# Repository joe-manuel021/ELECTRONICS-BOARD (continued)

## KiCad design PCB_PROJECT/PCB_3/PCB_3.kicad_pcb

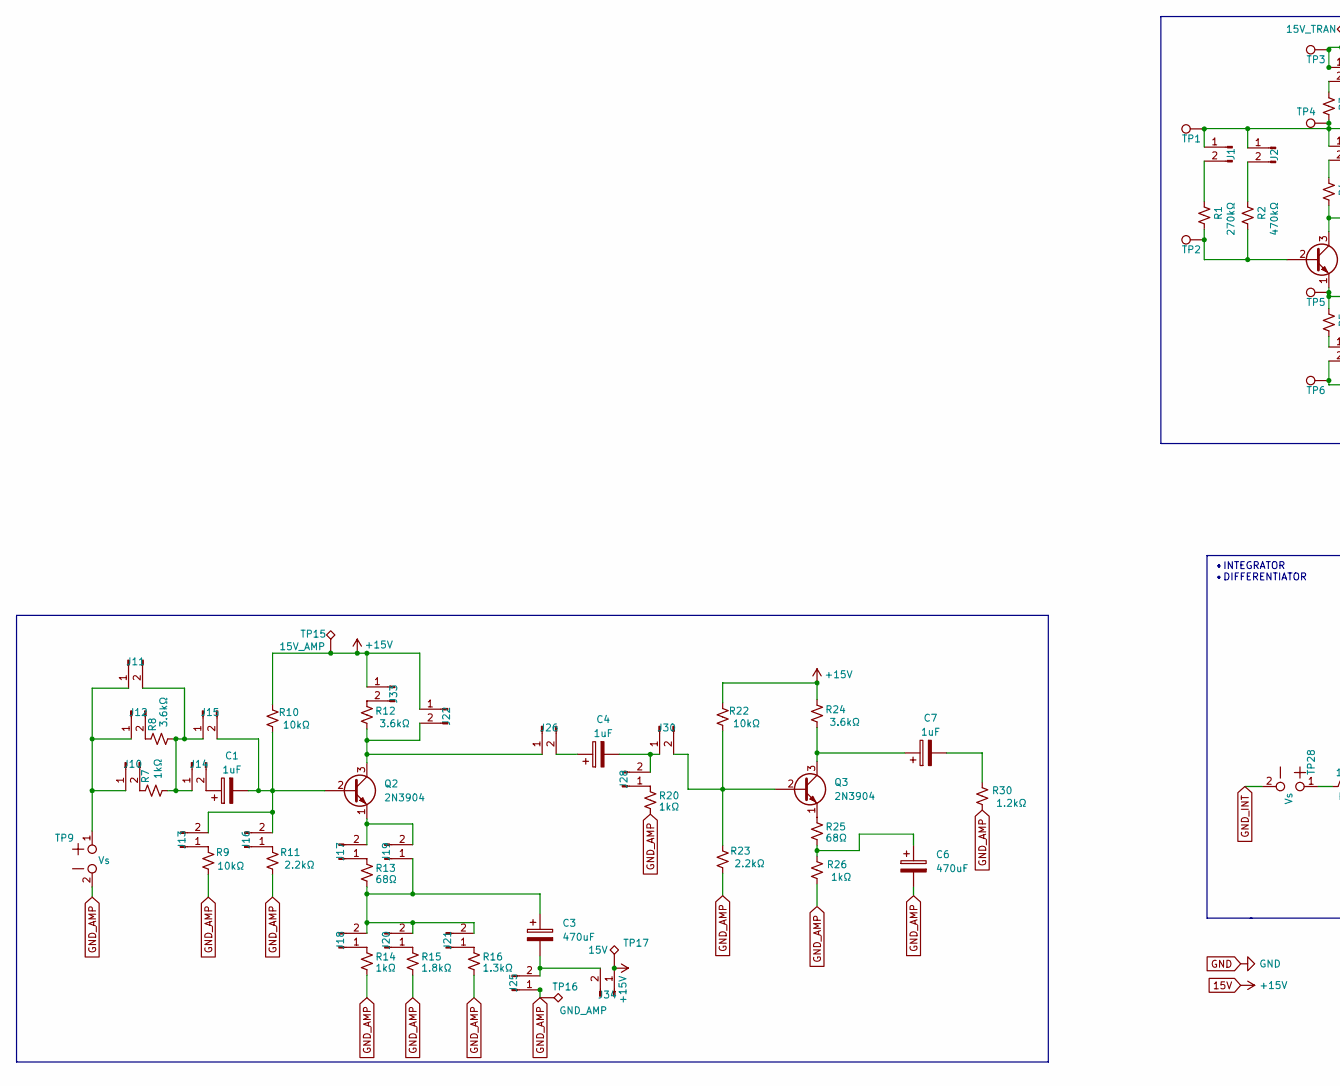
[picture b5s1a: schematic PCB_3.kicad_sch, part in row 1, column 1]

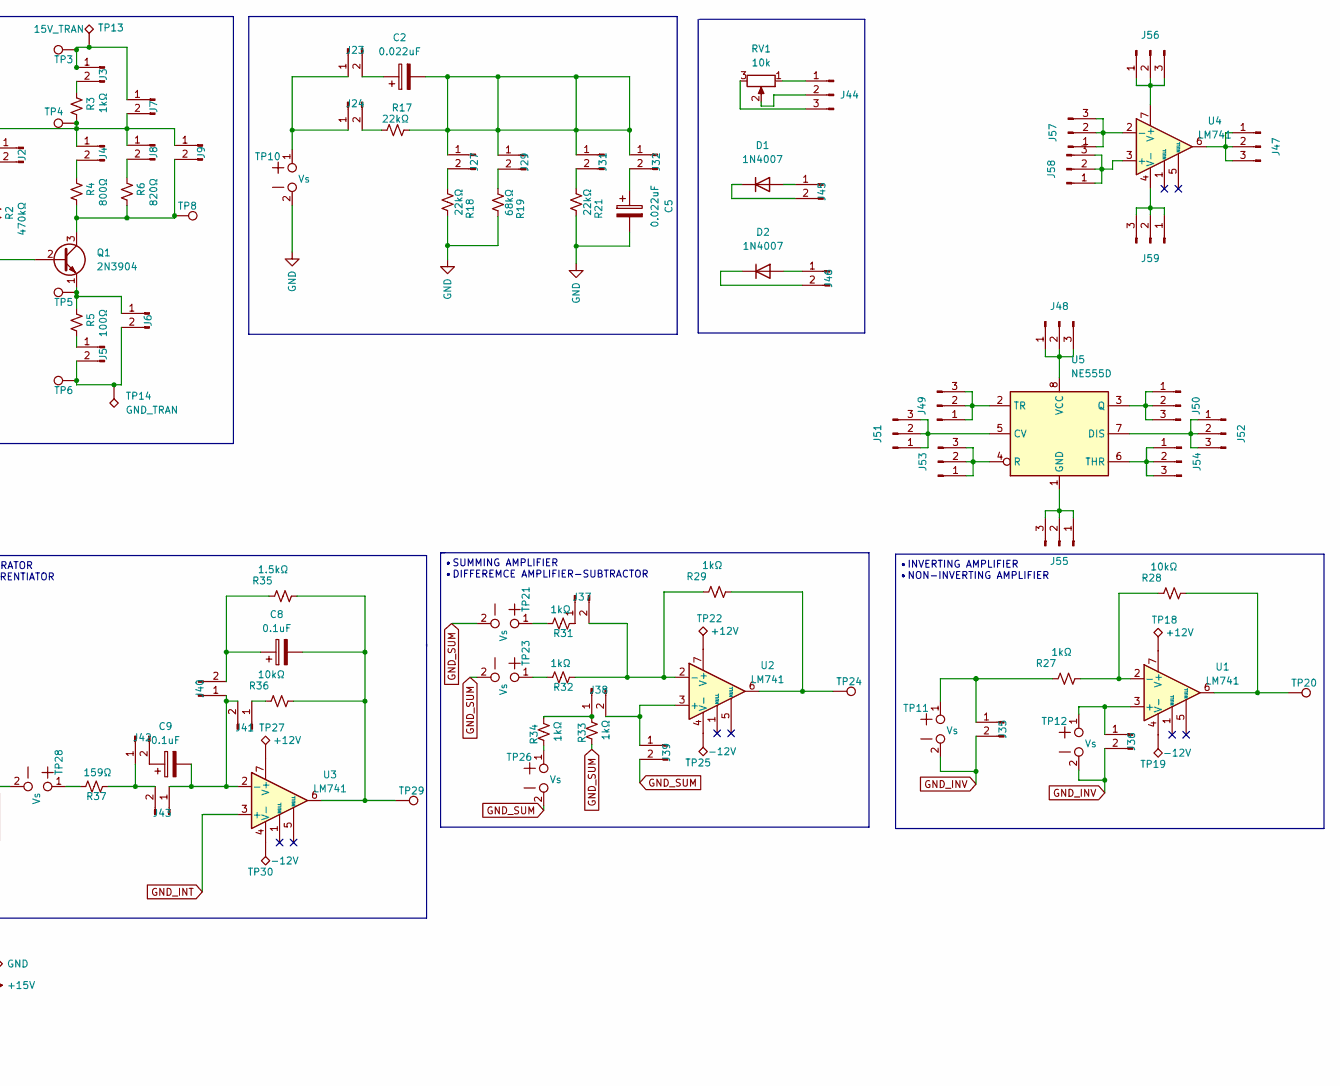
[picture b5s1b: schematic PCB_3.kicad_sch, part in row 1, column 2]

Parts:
C1, C4, C7: 1uF; CP_Radial_D5.0mm_P2.50mm
C2, C5: 0.022uF; 0.022uF_Capacitor
C3, C6: 470uF; CP_Radial_D10.0mm_P5.00mm
C8, C9: 0.1uF; 0.022uF_Capacitor
D1, D2: 1N4007; D_DO-41_SOD81_P10.16mm_Horizontal
J1, J2, J3, J4, J5, J6, J7, J8, J9, J10, J11, J12, J13, J14, J15, J16, J17, J18, J19, J20, J21, J22, J23, J24, J25, J26, J27, J28, J29, J30, J31, J32, J33, J34, J35, J36, J37, J38, J39, J40, J41, J42, J43, J45, J46: PinHeader_1x02_P2.54mm_Vertical_Blue
J44: W; PinHeader_1x03_P2.54mm_Vertical
J47, J48, J49, J50, J51, J52, J53, J54, J55, J56, J57, J58, J59: Conn_01x03_Male; PinHeader_1x03_P2.54mm_Vertical
Q1, Q2, Q3: 2N3904; TO-92_Inline
R1: 270kΩ; R_Axial_DIN0207_L6.3mm_D2.5mm_P10.16mm_Horizontal
R2: 470kΩ; R_Axial_DIN0207_L6.3mm_D2.5mm_P10.16mm_Horizontal
R3, R7, R14, R20, R26, R27, R29, R31, R32, R33, R34: 1kΩ; R_Axial_DIN0207_L6.3mm_D2.5mm_P10.16mm_Horizontal
R4: 800Ω; R_Axial_DIN0207_L6.3mm_D2.5mm_P10.16mm_Horizontal
R5: 100Ω; R_Axial_DIN0207_L6.3mm_D2.5mm_P10.16mm_Horizontal
R6: 820Ω; R_Axial_DIN0207_L6.3mm_D2.5mm_P10.16mm_Horizontal
R8, R12, R24: 3.6kΩ; R_Axial_DIN0207_L6.3mm_D2.5mm_P10.16mm_Horizontal
R9, R10, R22, R28, R36: 10kΩ; R_Axial_DIN0207_L6.3mm_D2.5mm_P10.16mm_Horizontal
R11, R23: 2.2kΩ; R_Axial_DIN0207_L6.3mm_D2.5mm_P10.16mm_Horizontal
R13, R25: 68Ω; R_Axial_DIN0207_L6.3mm_D2.5mm_P10.16mm_Horizontal
R15: 1.8kΩ; R_Axial_DIN0207_L6.3mm_D2.5mm_P10.16mm_Horizontal
R16: 1.3kΩ; R_Axial_DIN0207_L6.3mm_D2.5mm_P10.16mm_Horizontal
R17, R18, R21: 22kΩ; R_Axial_DIN0207_L6.3mm_D2.5mm_P10.16mm_Horizontal
R19: 68kΩ; R_Axial_DIN0207_L6.3mm_D2.5mm_P10.16mm_Horizontal
R30: 1.2kΩ; R_Axial_DIN0207_L6.3mm_D2.5mm_P10.16mm_Horizontal
R35: 1.5kΩ; R_Axial_DIN0207_L6.3mm_D2.5mm_P10.16mm_Horizontal
R37: 159Ω; R_Axial_DIN0207_L6.3mm_D2.5mm_P10.16mm_Horizontal
RV1: 10k; Potentiometer_Alps_RK09Y11_Single_Horizontal
TP1, TP2, TP3, TP4, TP5, TP6, TP8: 2.5_TP_1.5
TP9, TP10, TP11, TP12, TP21, TP23, TP26, TP28: Vs; TestPoint_Pith10mm_Drill4mm
TP13: 15V_TRAN; POWER_4MM
TP14: GND_TRAN; GND_4MM
TP15: 15V_AMP; POWER_4MM
TP16: GND_AMP; GND_4MM
TP17: 15V; POWER_4MM
TP18, TP22, TP27: +12V; GND_4MM
TP19, TP25, TP30: -12V; POWER_4MM
TP20, TP24, TP29: GND_4MM
U1, U2, U3, U4: LM741; DIP-8_W10.16mm_LongPads
U5: NE555D; DIP-8_W7.62mm_LongPads

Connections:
15V: J22.1, J33.1, J34.1, R10.2, R22.2, R24.2, TP15.1, TP17.1
GND: C5.2, R18.2, R19.2, R21.2, TP10.2
GND_AMP: C6.2, J25.1, R9.1, R11.1, R14.1, R15.1, R16.1, R20.1, R23.1, R26.1, R30.1, TP9.2, TP16.1
GND_INT: TP28.2, U3.3 (+)
GND_INV: J35.2, J36.2, TP11.2, TP12.2
GND_SUM: J39.2, R33.2, TP21.2, TP23.2, TP26.2
unnamed: C1.1, J14.2
unnamed: C1.2, J13.2, J15.2, J16.2, Q2.2 (B), R10.1
unnamed: C2.1, J23.2
unnamed: C2.2, J27.1, J29.1, J31.1, J32.1, R17.2
unnamed: C3.1, J18.2, J19.1, J20.2, J21.2, R13.1
unnamed: C3.2, J25.2, J34.2
unnamed: C4.1, J26.2
unnamed: C4.2, J28.2, J30.1
unnamed: C5.1, J32.2
unnamed: C6.1, R25.1, R26.2
unnamed: C7.1, Q3.3 (C), R24.1
unnamed: C7.2, R30.2
unnamed: C8.1, J40.2, R35.2
unnamed: C8.2, R35.1, R36.1, TP29.1, U3.6
unnamed: C9.1, J42.2
unnamed: C9.2, J40.1, J41.2, J43.1, U3.2 (-)
unnamed: D1.1 (K), J45.2
unnamed: D1.2 (A), J45.1
unnamed: D2.1 (K), J46.2
unnamed: D2.2 (A), J46.1
unnamed: J1.1, J2.1, J4.1, J7.2, J8.1, J9.1, R3.2, TP1.1, TP4.1
unnamed: J1.2, R1.1
unnamed: J2.2, R2.1
unnamed: J3.1, J7.1, TP3.1, TP13.1
unnamed: J3.2, R3.1
unnamed: J4.2, R4.1
unnamed: J5.1, R5.2
unnamed: J5.2, J6.2, TP6.1, TP14.1
unnamed: J6.1, Q1.1 (E), R5.1, TP5.1
unnamed: J8.2, R6.1
unnamed: J9.2, Q1.3 (C), R4.2, R6.2, TP8.1
unnamed: J10.1, J11.1, J12.1, TP9.1
unnamed: J10.2, R7.2
unnamed: J11.2, J14.1, J15.1, R7.1, R8.1
unnamed: J12.2, R8.2
unnamed: J13.1, R9.2
unnamed: J16.1, R11.2
unnamed: J17.1, R13.2
unnamed: J17.2, J19.2, Q2.1 (E)
unnamed: J18.1, R14.2
unnamed: J20.1, R15.2
unnamed: J21.1, R16.2
unnamed: J22.2, J26.1, Q2.3 (C), R12.1
unnamed: J23.1, J24.1, TP10.1
unnamed: J24.2, R17.1
unnamed: J27.2, R18.1
unnamed: J28.1, R20.2
unnamed: J29.2, R19.1
unnamed: J30.2, Q3.2 (B), R22.1, R23.2
unnamed: J31.2, R21.1
unnamed: J33.2, R12.2
unnamed: J35.1, R27.2, TP11.1
unnamed: J36.1, TP12.1, U1.3 (+)
unnamed: J37.1, R31.2
unnamed: J37.2, R29.2, R32.2, U2.2 (-)
unnamed: J38.1, R33.1, R34.1
unnamed: J38.2, J39.1, U2.3 (+)
unnamed: J41.1, R36.2
unnamed: J42.1, J43.2, R37.2
unnamed: J44.1, RV1.1
unnamed: J44.2, RV1.2
unnamed: J44.3, RV1.3
unnamed: J47.1, J47.2, J47.3, U4.6
unnamed: J48.1, J48.2, J48.3, U5.8 (VCC)
unnamed: J49.1, J49.2, J49.3, U5.2 (TR)
unnamed: J50.1, J50.2, J50.3, U5.3 (Q)
unnamed: J51.1, J51.2, J51.3, U5.5 (CV)
unnamed: J52.1, J52.2, J52.3, U5.7 (DIS)
unnamed: J53.1, J53.2, J53.3, U5.4 (R)
unnamed: J54.1, J54.2, J54.3, U5.6 (THR)
unnamed: J55.1, J55.2, J55.3, U5.1 (GND)
unnamed: J56.1, J56.2, J56.3, U4.7 (V+)
unnamed: J57.1, J57.2, J57.3, U4.2 (-)
unnamed: J58.1, J58.2, J58.3, U4.3 (+)
unnamed: J59.1, J59.2, J59.3, U4.4 (V-)
unnamed: Q1.2 (B), R1.2, R2.2, TP2.1
unnamed: Q3.1 (E), R25.2
unnamed: R27.1, R28.2, U1.2 (-)
unnamed: R28.1, TP20.1, U1.6
unnamed: R29.1, TP24.1, U2.6
unnamed: R31.1, TP21.1
unnamed: R32.1, TP23.1
unnamed: R34.2, TP26.1
unnamed: R37.1, TP28.1
unnamed: TP18.1, U1.7 (V+)
unnamed: TP19.1, U1.4 (V-)
unnamed: TP22.1, U2.7 (V+)
unnamed: TP25.1, U2.4 (V-)
unnamed: TP27.1, U3.7 (V+)
unnamed: TP30.1, U3.4 (V-)

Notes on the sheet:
•INVERTING AMPLIFIER •NON-INVERTING AMPLIFIER
•SUMMING AMPLIFIER •DIFFEREMCE AMPLIFIER-SUBTRACTOR
•INTEGRATOR •DIFFERENTIATOR

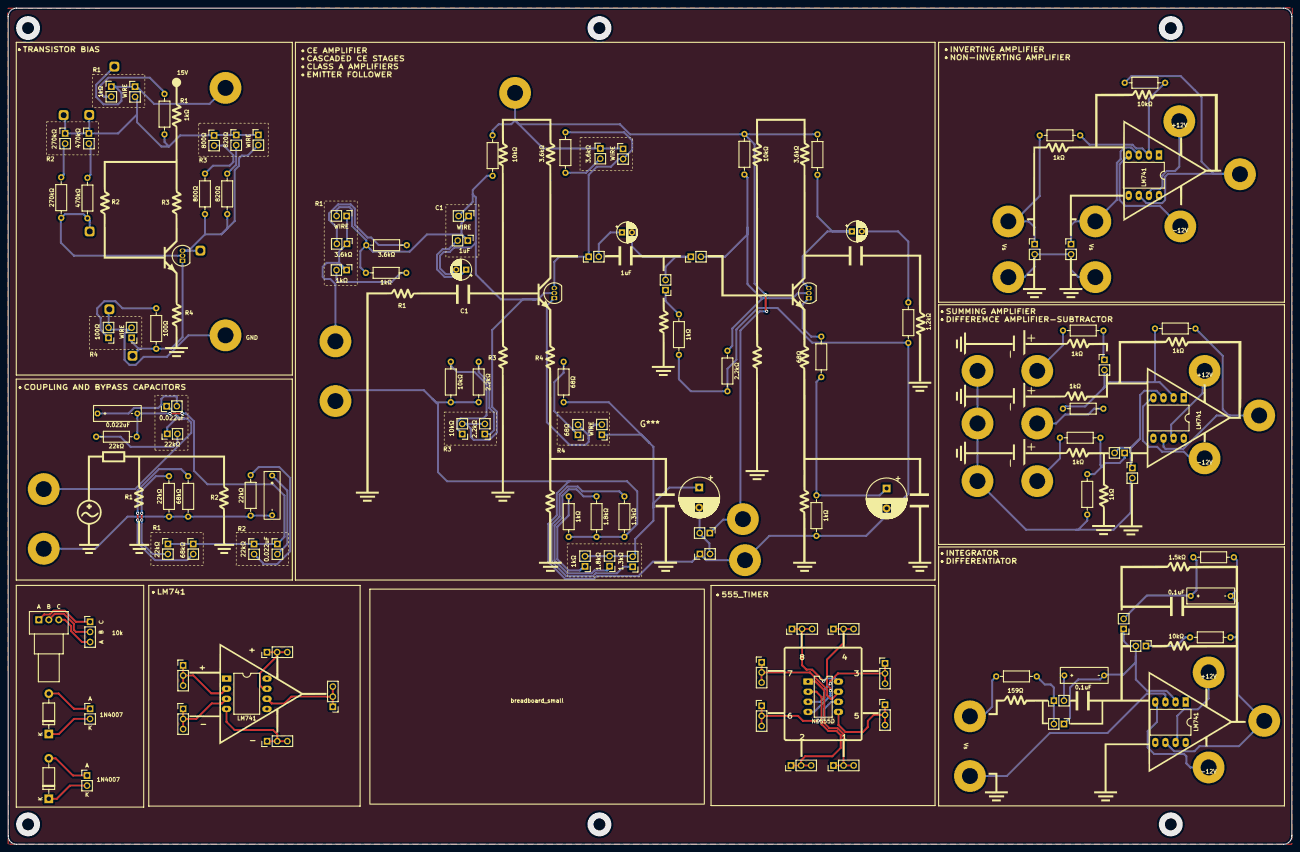
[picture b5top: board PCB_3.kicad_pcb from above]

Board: 2 copper layers, 322.4 x 210.0 mm, 145 parts (0 on the bottom side), 96 nets.

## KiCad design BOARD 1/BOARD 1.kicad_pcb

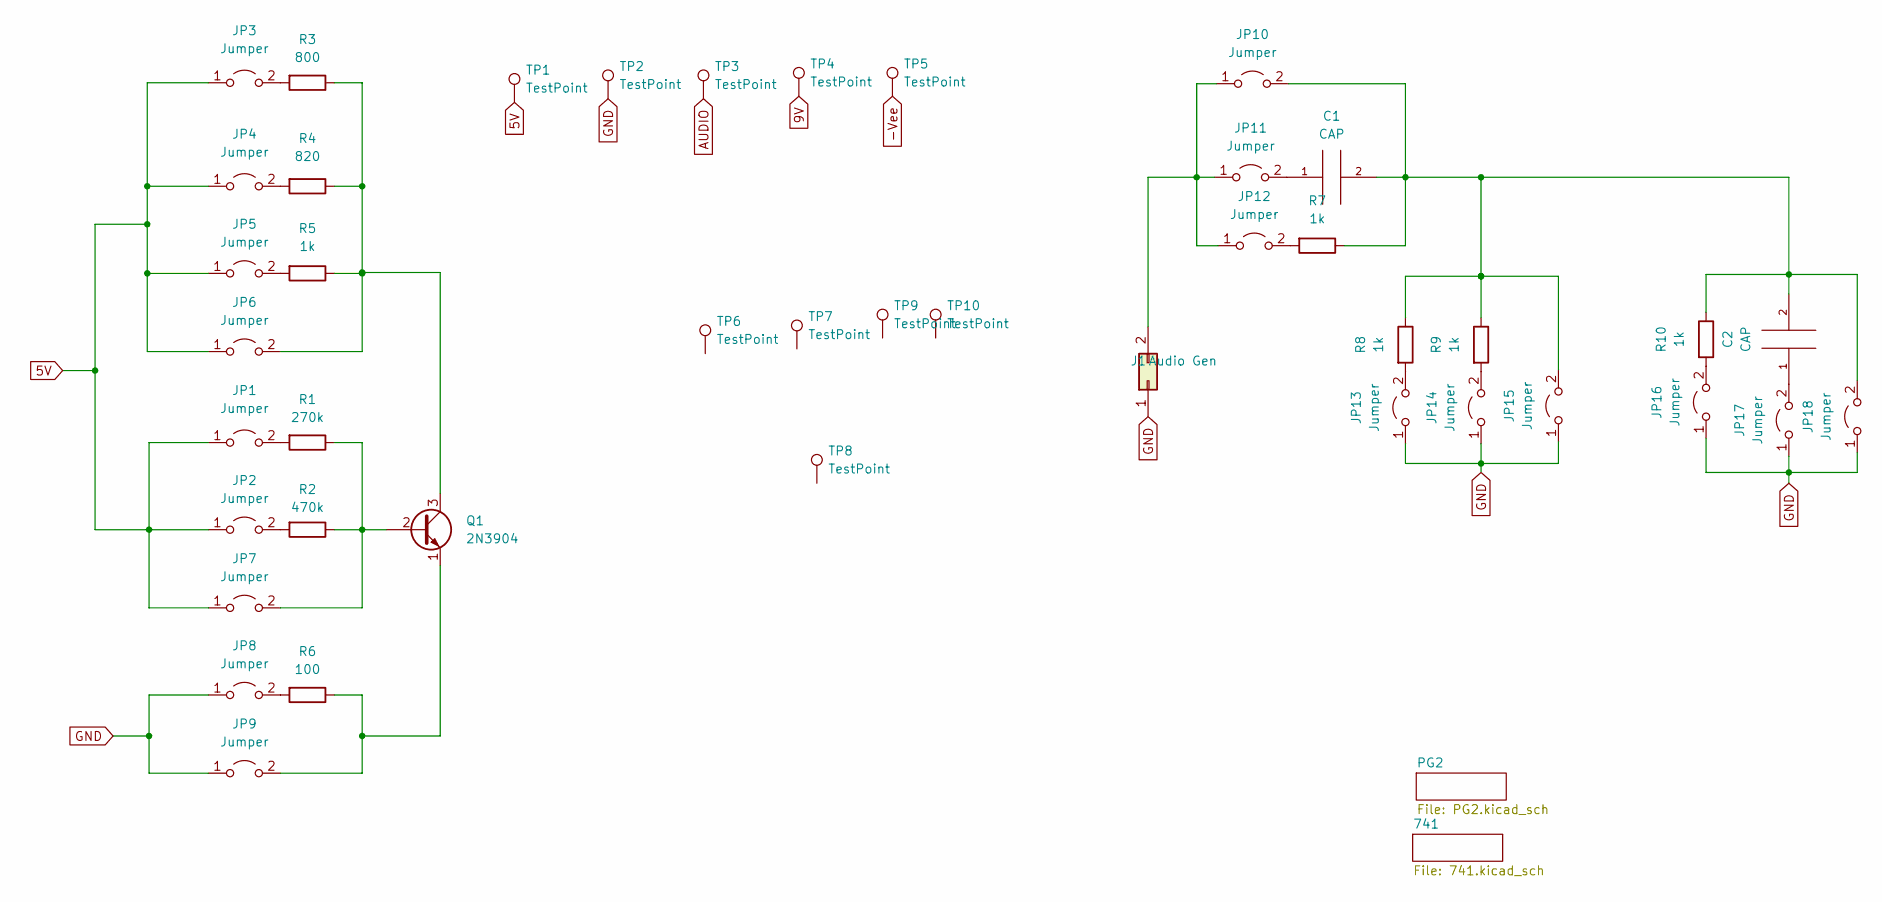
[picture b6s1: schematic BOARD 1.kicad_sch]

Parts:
C1, C2: CAP; CP_Radial_D5.0mm_P2.00mm
J1: Audio Gen; PinHeader_1x02_P2.54mm_Vertical
JP1, JP2, JP3, JP4, JP5, JP6, JP7, JP8, JP9, JP10, JP11, JP12, JP13, JP14, JP15, JP16, JP17, JP18: Jumper; PinHeader_1x02_P2.54mm_Vertical
Q1: 2N3904; TO-92_Inline
R1: 270k; R_Axial_DIN0309_L9.0mm_D3.2mm_P12.70mm_Horizontal
R2: 470k; R_Axial_DIN0309_L9.0mm_D3.2mm_P12.70mm_Horizontal
R3: 800; R_Axial_DIN0309_L9.0mm_D3.2mm_P12.70mm_Horizontal
R4: 820; R_Axial_DIN0309_L9.0mm_D3.2mm_P12.70mm_Horizontal
R5, R7, R8, R9, R10: 1k; R_Axial_DIN0309_L9.0mm_D3.2mm_P12.70mm_Horizontal
R6: 100; R_Axial_DIN0309_L9.0mm_D3.2mm_P12.70mm_Horizontal
TP1, TP2, TP3, TP4, TP5, TP6, TP7, TP8, TP9, TP10: TestPoint; TestPoint_Plated_Hole_D5.0mm

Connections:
5V: JP1.1 (A), JP2.1 (A), JP3.1 (A), JP4.1 (A), JP5.1 (A), JP6.1 (A), JP7.1 (A), TP1.1; also elsewhere on the board
GND: J1.1 (Pin_a1), JP8.1 (A), JP9.1 (A), JP13.1 (A), JP14.1 (A), JP15.1 (A), JP16.1 (A), JP17.1 (A), JP18.1 (A), TP2.1; also elsewhere on the board
unnamed 6: C1.1, JP11.2 (B); also elsewhere on the board
unnamed 7: C1.2, JP10.2 (B), JP15.2 (B), R7.1, R8.1, R9.1; also elsewhere on the board
unnamed: C2.1, JP17.2 (B)
unnamed 9: C2.2, JP18.2 (B), R10.1; also elsewhere on the board
unnamed 20: J1.2 (Pin_b1), JP10.1 (A), JP11.1 (A), JP12.1 (A); also elsewhere on the board
unnamed: JP1.2 (B), R1.2
unnamed: JP2.2 (B), R2.2
unnamed: JP3.2 (B), R3.2
unnamed: JP4.2 (B), R4.2
unnamed: JP5.2 (B), R5.2
unnamed: JP6.2 (B), Q1.3 (C), R3.1, R4.1, R5.1
unnamed: JP7.2 (B), Q1.2 (B), R1.1, R2.1
unnamed: JP8.2 (B), R6.2
unnamed: JP9.2 (B), Q1.1 (E), R6.1
unnamed 36: JP12.2 (B), R7.2; also elsewhere on the board
unnamed: JP13.2 (B), R8.2
unnamed: JP14.2 (B), R9.2
unnamed 39: JP16.2 (B), R10.2; also elsewhere on the board

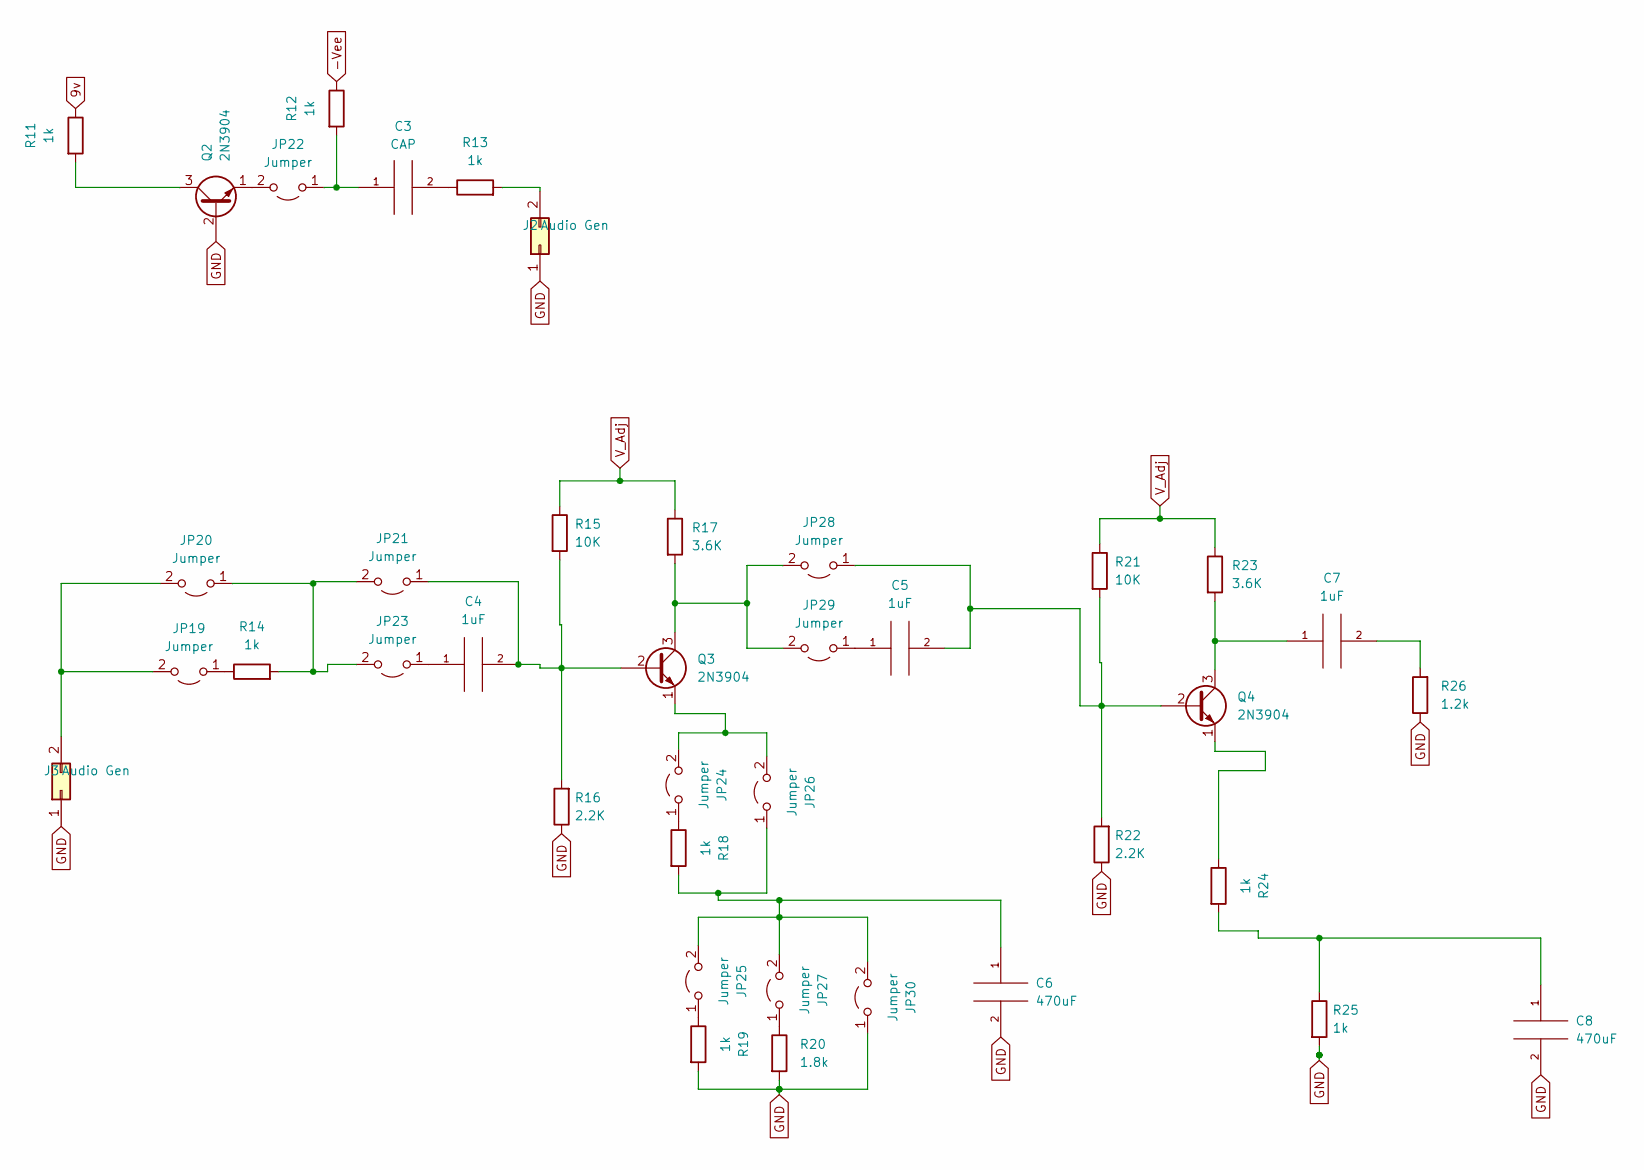
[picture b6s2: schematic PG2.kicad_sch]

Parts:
C3: CAP; CP_Radial_D5.0mm_P2.00mm
C4, C5, C7: 1uF; CP_Radial_D5.0mm_P2.00mm
C6, C8: 470uF; CP_Radial_D5.0mm_P2.00mm
J2, J3: Audio Gen; PinHeader_1x02_P2.54mm_Vertical
JP19, JP20, JP21, JP22, JP23, JP24, JP25, JP26, JP27, JP28, JP29, JP30: Jumper; PinHeader_1x02_P2.54mm_Vertical
Q2, Q3, Q4: 2N3904; TO-92_Inline
R11, R12, R13, R14, R18, R19, R24, R25: 1k; R_Axial_DIN0309_L9.0mm_D3.2mm_P12.70mm_Horizontal
R15, R21: 10K; R_Axial_DIN0309_L9.0mm_D3.2mm_P12.70mm_Horizontal
R16, R22: 2.2K; R_Axial_DIN0309_L9.0mm_D3.2mm_P12.70mm_Horizontal
R17, R23: 3.6K; R_Axial_DIN0309_L9.0mm_D3.2mm_P12.70mm_Horizontal
R20: 1.8k; R_Axial_DIN0309_L9.0mm_D3.2mm_P12.70mm_Horizontal
R26: 1.2k; R_Axial_DIN0309_L9.0mm_D3.2mm_P12.70mm_Horizontal

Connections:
9v: R11.1
-Vee: R12.1
GND: C6.2, C8.2, J2.1 (Pin_a1), J3.1 (Pin_a1), JP30.1 (A), Q2.2 (B), R16.1, R19.2, R20.2, R22.1, R25.2, R26.1; also elsewhere on the board
unnamed: C3.1, JP22.1 (A), R12.2
unnamed: C3.2, R13.1
unnamed: C4.1, JP23.1 (A)
unnamed: C4.2, JP21.1 (A), Q3.2 (B), R15.2, R16.2
unnamed: C5.1, JP29.1 (A)
unnamed: C5.2, JP28.1 (A), Q4.2 (B), R21.2, R22.2
unnamed: C6.1, JP25.2 (B), JP26.1 (A), JP27.2 (B), JP30.2 (B), R18.2
unnamed: C7.1, Q4.3 (C), R23.2
unnamed: C7.2, R26.2
unnamed: C8.1, R24.2, R25.1
unnamed: J2.2 (Pin_b1), R13.2
unnamed: J3.2 (Pin_b1), JP19.2 (B), JP20.2 (B)
unnamed: JP19.1 (A), R14.1
unnamed: JP20.1 (A), JP21.2 (B), JP23.2 (B), R14.2
unnamed: JP22.2 (B), Q2.1 (E)
unnamed: JP24.1 (A), R18.1
unnamed: JP24.2 (B), JP26.2 (B), Q3.1 (E)
unnamed: JP25.1 (A), R19.1
unnamed: JP27.1 (A), R20.1
unnamed: JP28.2 (B), JP29.2 (B), Q3.3 (C), R17.2
unnamed: Q2.3 (C), R11.2
unnamed: Q4.1 (E), R24.1
V_Adj: R15.1, R17.1, R21.1, R23.1

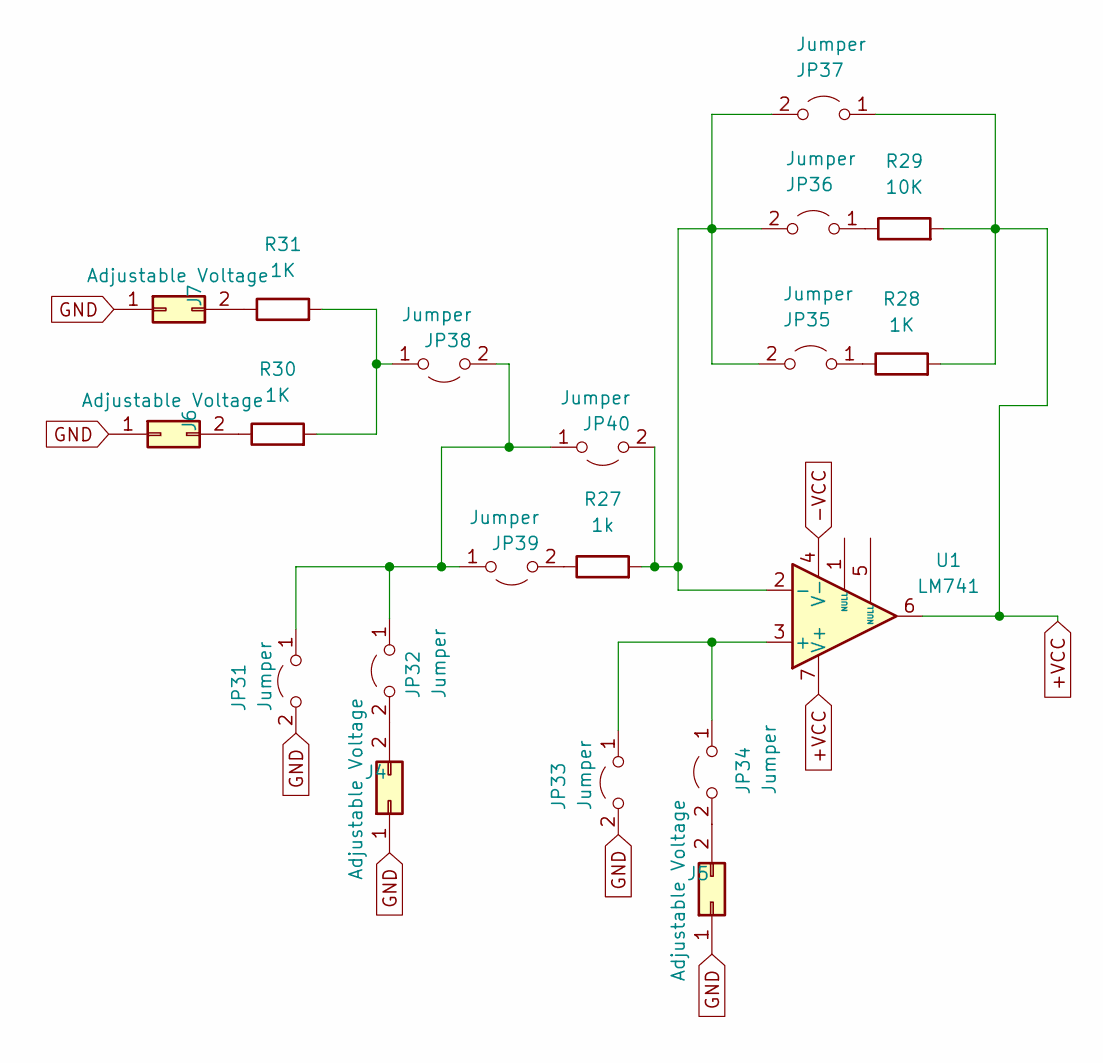
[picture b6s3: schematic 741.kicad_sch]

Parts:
J4, J5, J6, J7: Adjustable Voltage; PinHeader_1x02_P2.54mm_Vertical
JP31, JP32, JP33, JP34, JP35, JP36, JP37, JP38, JP39, JP40: Jumper; PinHeader_1x02_P2.54mm_Vertical
R27: 1k; R_Axial_DIN0309_L9.0mm_D3.2mm_P12.70mm_Horizontal
R28, R30, R31: 1K; R_Axial_DIN0309_L9.0mm_D3.2mm_P12.70mm_Horizontal
R29: 10K; R_Axial_DIN0309_L9.0mm_D3.2mm_P12.70mm_Horizontal
U1: LM741; DIP-8_W10.16mm_LongPads

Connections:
+VCC: JP37.1 (A), R28.2, R29.2, U1.6, U1.7 (V+)
-VCC: U1.4 (V-)
GND: J4.1 (Pin_a1), J5.1 (Pin_a1), J6.1 (Pin_a1), J7.1 (Pin_a1), JP31.2 (B), JP33.2 (B); also elsewhere on the board
unnamed: J4.2 (Pin_b1), JP32.2 (B)
unnamed: J5.2 (Pin_b1), JP34.2 (B)
unnamed: J6.2 (Pin_b1), R30.1
unnamed: J7.2 (Pin_b1), R31.1
unnamed: JP31.1 (A), JP32.1 (A), JP38.2 (B), JP39.1 (A), JP40.1 (A)
unnamed: JP33.1 (A), JP34.1 (A), U1.3 (+)
unnamed: JP35.1 (A), R28.1
unnamed: JP35.2 (B), JP36.2 (B), JP37.2 (B), JP40.2 (B), R27.2, U1.2 (-)
unnamed: JP36.1 (A), R29.1
unnamed: JP38.1 (A), R30.2, R31.2
unnamed: JP39.2 (B), R27.1

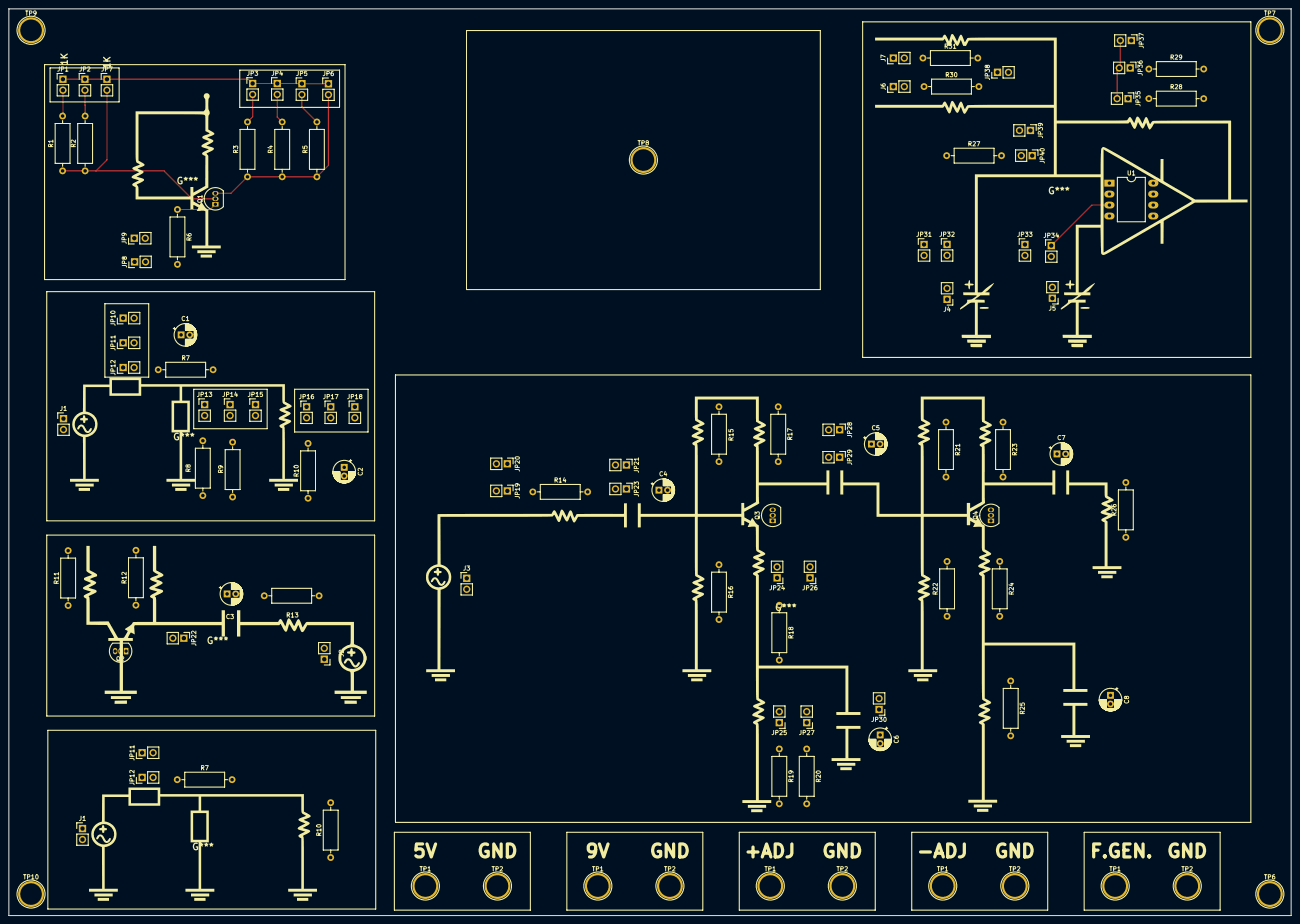
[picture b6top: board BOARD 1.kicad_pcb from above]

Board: 2 copper layers, 297.0 x 210.0 mm, 111 parts (0 on the bottom side), 55 nets.

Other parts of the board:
J1#2: Audio Gen; PinHeader_1x02_P2.54mm_Vertical
JP11#2, JP12#2: Jumper; PinHeader_1x02_P2.54mm_Vertical
R7#2, R10#2: 1k; R_Axial_DIN0309_L9.0mm_D3.2mm_P12.70mm_Horizontal
TP1#2, TP1#3, TP1#4, TP1#5, TP2#2, TP2#3, TP2#4, TP2#5: TestPoint; TestPoint_Plated_Hole_D5.0mm

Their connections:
5V: TP1#2.1, TP1#3.1, TP1#4.1, TP1#5.1; also elsewhere on the board
GND: J1#2.1 (Pin_a1), TP2#2.1, TP2#3.1, TP2#4.1, TP2#5.1; also elsewhere on the board
unnamed 6: JP11#2.2 (B); also elsewhere on the board
unnamed 7: R7#2.1; also elsewhere on the board
unnamed 9: R10#2.1; also elsewhere on the board
unnamed 20: J1#2.2 (Pin_b1), JP11#2.1 (A), JP12#2.1 (A); also elsewhere on the board
unnamed 36: JP12#2.2 (B), R7#2.2; also elsewhere on the board
unnamed 39: R10#2.2; also elsewhere on the board

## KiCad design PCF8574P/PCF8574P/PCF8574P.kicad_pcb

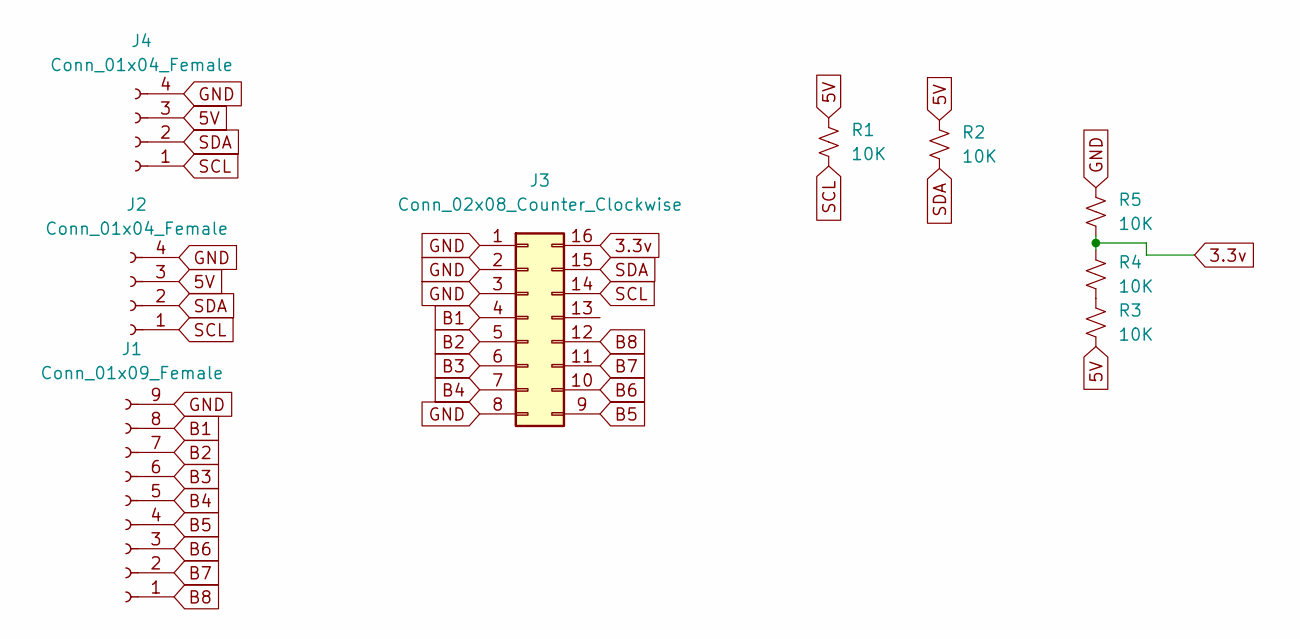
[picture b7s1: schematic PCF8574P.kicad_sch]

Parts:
J1: Conn_01x09_Female; PinHeader_1x09_P2.54mm_Vertical
J2, J4: Conn_01x04_Female; PinHeader_1x04_P2.54mm_Vertical
J3: Conn_02x08_Counter_Clockwise; DIP-16_W7.62mm_Socket_LongPads
R1, R2, R3, R4, R5: 10K; R_Axial_DIN0204_L3.6mm_D1.6mm_P7.62mm_Horizontal

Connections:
3.3v: J3.16, R4.1, R5.2
5V: J2.3, J4.3, R1.1, R2.1, R3.2
B1: J1.8, J3.4
B2: J1.7, J3.5
B3: J1.6, J3.6
B4: J1.5, J3.7
B5: J1.4, J3.9
B6: J1.3, J3.10
B7: J1.2, J3.11
B8: J1.1, J3.12
GND: J1.9, J2.4, J3.1, J3.2, J3.3, J3.8, J4.4, R5.1
unnamed: R3.1, R4.2
SCL: J2.1, J3.14, J4.1, R1.2
SDA: J2.2, J3.15, J4.2, R2.2

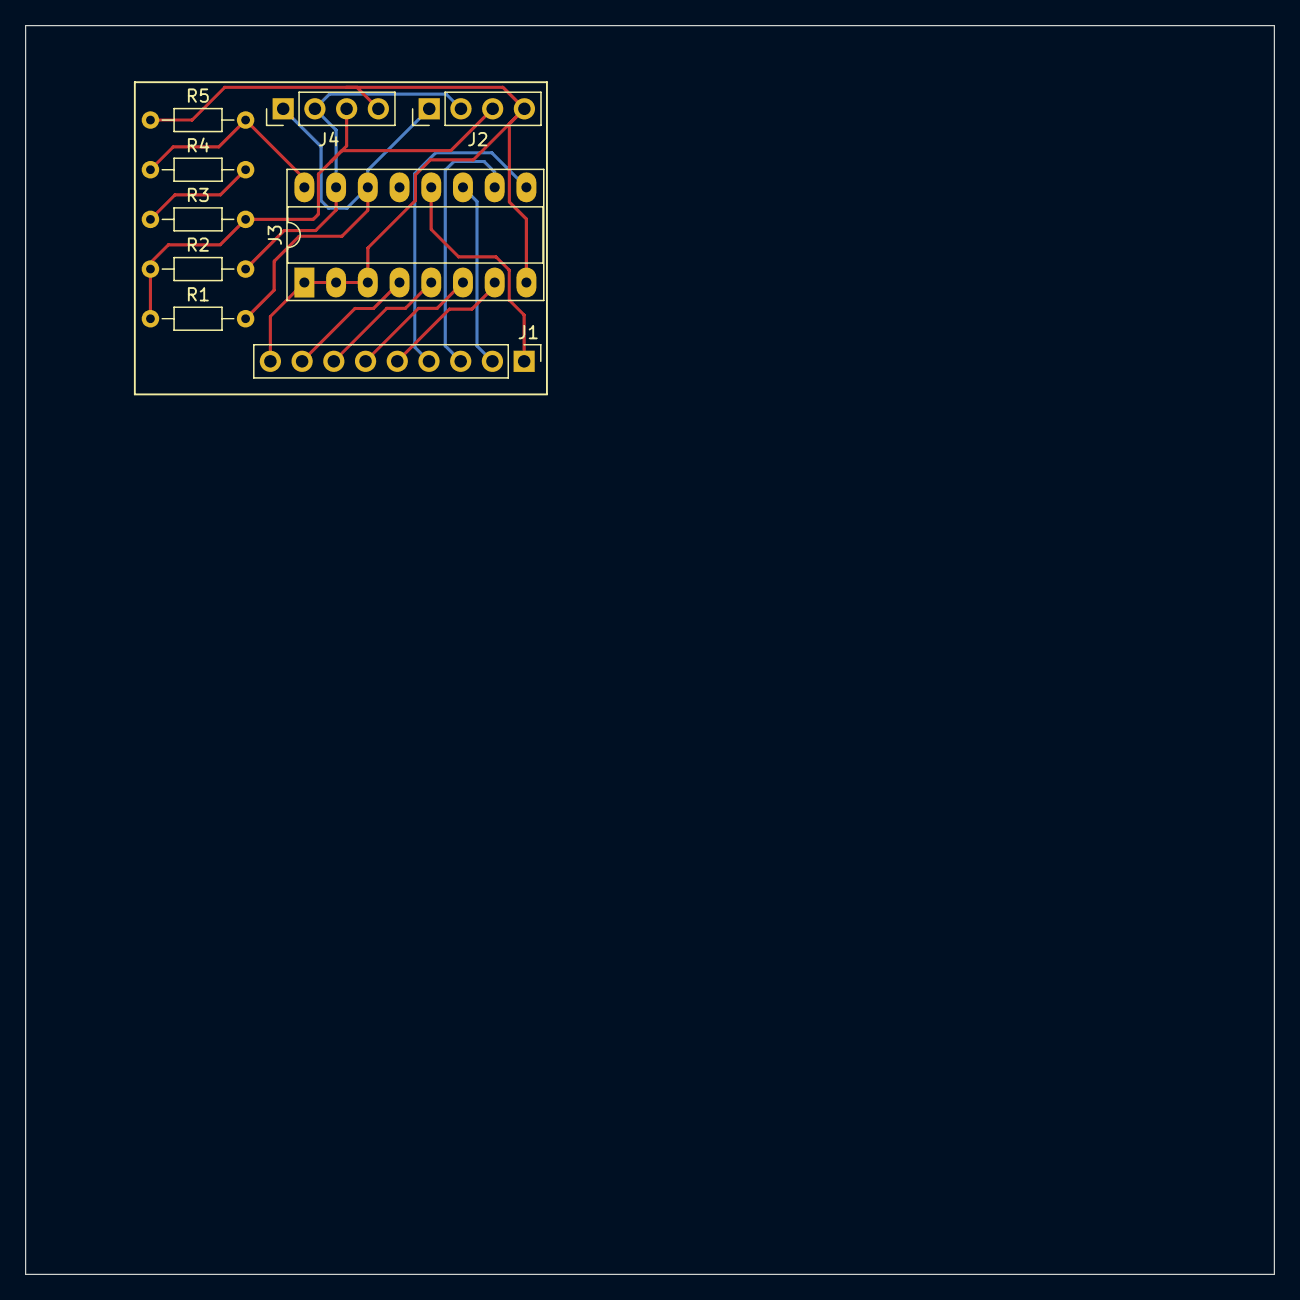
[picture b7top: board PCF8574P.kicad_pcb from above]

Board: 2 copper layers, 100.0 x 100.0 mm, 9 parts (0 on the bottom side), 14 nets.

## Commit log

2024-09-09 PCB COMPILATION
2024-09-09 updated File
2024-09-13 Before Finalize
2024-09-14 LATEST FILE WITH GBR
    LOCATION-
    PCB_PROJECT
    GBR
